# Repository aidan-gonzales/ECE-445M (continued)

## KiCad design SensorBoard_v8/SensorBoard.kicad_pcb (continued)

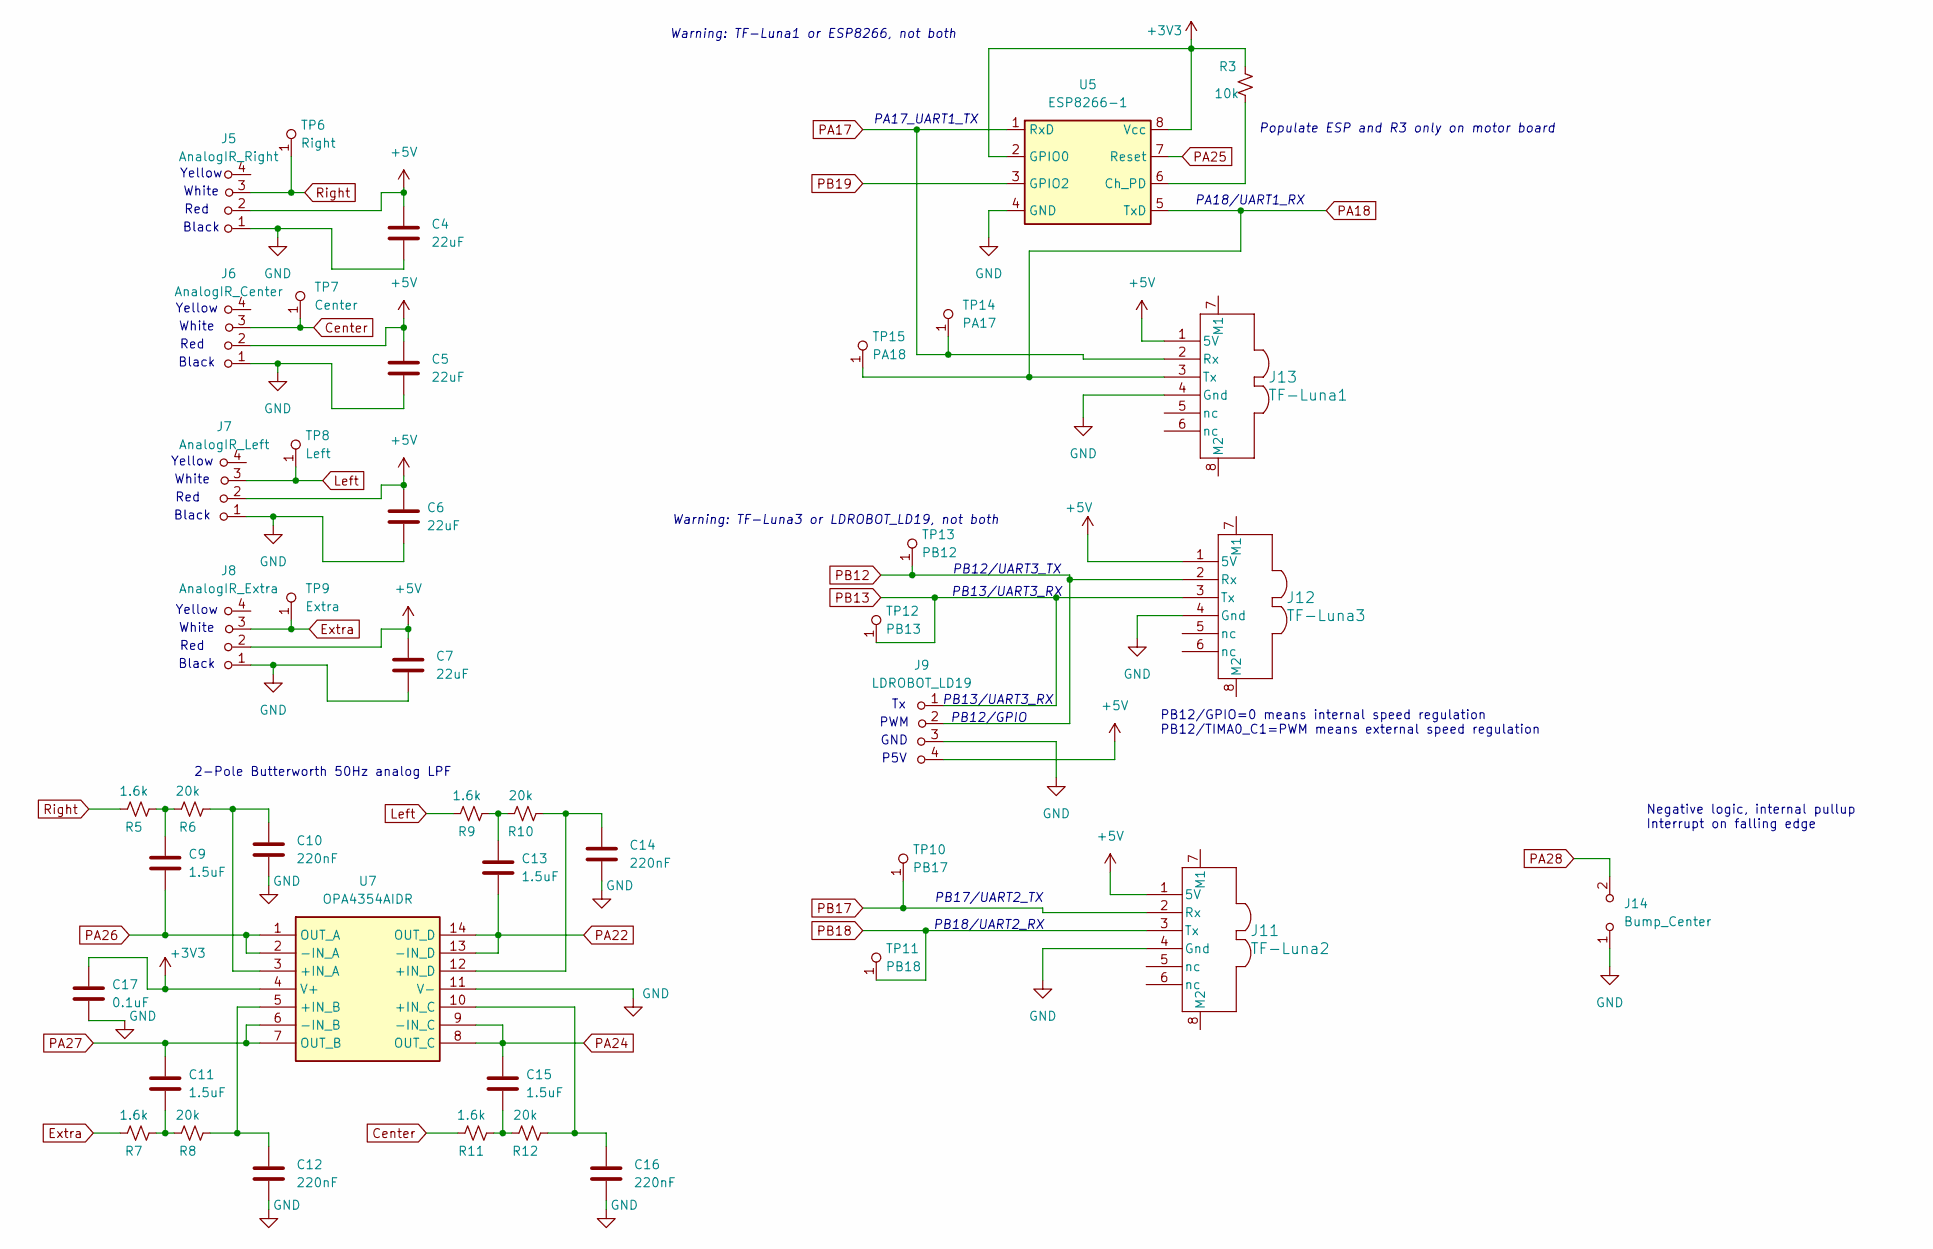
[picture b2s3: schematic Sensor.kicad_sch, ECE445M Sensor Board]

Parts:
C4, C5, C6, C7: 22uF; C_0805_2012Metric; LCSC C5186689
C9, C11, C13, C15: 1.5uF; C_0603_1608Metric; LCSC C5186689
C10, C12, C14, C16: 220nF; C_0603_1608Metric; LCSC C5186689
C17: 0.1uF; C_0603_1608Metric; LCSC C5186689
J5: AnalogIR_Right; PinHeader_1x04_P2.00mm_Horizontal; Mouser 713-110990037
J6: AnalogIR_Center; PinHeader_1x04_P2.00mm_Horizontal; Mouser 713-110990037
J7: AnalogIR_Left; PinHeader_1x04_P2.00mm_Horizontal; Mouser 713-110990037
J8: AnalogIR_Extra; PinHeader_1x04_P2.00mm_Horizontal; Mouser 713-110990037
J9: LDROBOT_LD19; PinHeader_1x04_P2.00mm_Horizontal_JST; Mouser 306-S04BPASK2LFSN
J11: TF-Luna2; CONN_SM06B-GHS-TB_JST; Digikey WM7624CT-ND
J12: TF-Luna3; CONN_SM06B-GHS-TB_JST; Digikey WM7624CT-ND
J13: TF-Luna1; CONN_SM06B-GHS-TB_JST; Digikey WM7624CT-ND
J14: Bump_Center; PinHeader_1x02_P2.54mm_Vertical
R3: 10k; R_Axial_DIN0204_L3.6mm_D1.6mm_P7.62mm_Horizontal
R5, R7, R9, R11: 1.6k; R_0603_1608Metric; LCSC C340542
R6, R8, R10, R12: 20k; R_0603_1608Metric; LCSC C340542
TP6: Right; Testpoint_1x1; Digikey 36-5000-ND, 36-5001-ND, 36-5002-ND , 36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
TP7: Center; Testpoint_1x1; Digikey 36-5000-ND, 36-5001-ND, 36-5002-ND , 36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
TP8: Left; Testpoint_1x1; Digikey 36-5000-ND, 36-5001-ND, 36-5002-ND , 36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
TP9: Extra; Testpoint_1x1; Digikey 36-5000-ND, 36-5001-ND, 36-5002-ND , 36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
TP10: PB17; Testpoint_1x1; Digikey 36-5000-ND, 36-5001-ND, 36-5002-ND , 36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
TP11: PB18; Testpoint_1x1; Digikey 36-5000-ND, 36-5001-ND, 36-5002-ND , 36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
TP12: PB13; Testpoint_1x1; Digikey 36-5000-ND, 36-5001-ND, 36-5002-ND , 36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
TP13: PB12; Testpoint_1x1; Digikey 36-5000-ND, 36-5001-ND, 36-5002-ND , 36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
TP14: PA17; Testpoint_1x1; Digikey 36-5000-ND, 36-5001-ND, 36-5002-ND , 36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
TP15: PA18; Testpoint_1x1; Digikey 36-5000-ND, 36-5001-ND, 36-5002-ND , 36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
U5: ESP8266-1; PinHeader_2x04_P2.54mm_Vertical
U7: OPA4354AIDR; SOIC127P600X175-14N; Mouser Part Number 595-OPA4354AIDR

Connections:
+3V3: C17.1, R3.1, U5.2 (GPIO0), U5.8 (Vcc), U7.4 (V+); also elsewhere on the board
+5V: C4.1, C5.1, C6.1, C7.1, J5.2 (5V), J6.2 (5V), J7.2 (5V), J8.2 (5V), J9.4 (5V), J11.1 (5V), J12.1 (5V), J13.1 (5V); also elsewhere on the board
Center: J6.3 (Vin), R11.1, TP7.1 (A)
Extra: J8.3 (Vin), R7.1, TP9.1 (A)
GND: C4.2, C5.2, C6.2, C7.2, C10.2, C12.2, C14.2, C16.2, C17.2, J5.1 (Gnd), J6.1 (Gnd), J7.1 (Gnd), J8.1 (Gnd), J9.3 (GND), J11.4 (Gnd), J12.4 (Gnd), J13.4 (Gnd), J14.1 (A), U5.4 (GND), U7.11 (V-); also elsewhere on the board
Left: J7.3 (Vin), R9.1, TP8.1 (A)
unnamed: C9.1, R5.2, R6.1
unnamed: C11.2, R7.2, R8.1
unnamed: C13.1, R9.2, R10.1
unnamed: C15.2, R11.2, R12.1
unnamed: R3.2, U5.6 (Ch_PD)
unnamed: C10.1, R6.2, U7.3 (+IN_A)
unnamed: C12.1, R8.2, U7.5 (+IN_B)
unnamed: C16.1, R12.2, U7.10 (+IN_C)
unnamed: C14.1, R10.2, U7.12 (+IN_D)
PA17: J13.2 (Rx), TP14.1 (A), U5.1 (RxD); also elsewhere on the board
PA18: J13.3 (Tx), TP15.1 (A), U5.5 (TxD); also elsewhere on the board
PA22: C13.2, U7.13 (-IN_D), U7.14 (OUT_D); also elsewhere on the board
PA24: C15.1, U7.8 (OUT_C), U7.9 (-IN_C); also elsewhere on the board
PA25: U5.7 (Reset); also elsewhere on the board
PA26: C9.2, U7.1 (OUT_A), U7.2 (-IN_A); also elsewhere on the board
PA27: C11.1, U7.6 (-IN_B), U7.7 (OUT_B); also elsewhere on the board
PA28: J14.2 (B); also elsewhere on the board
PB12: J9.2 (PWM), J12.2 (Rx), TP13.1 (A); also elsewhere on the board
PB13: J9.1 (Tx), J12.3 (Tx), TP12.1 (A); also elsewhere on the board
PB17: J11.2 (Rx), TP10.1 (A); also elsewhere on the board
PB18: J11.3 (Tx), TP11.1 (A); also elsewhere on the board
PB19: U5.3 (GPIO2); also elsewhere on the board
Right: J5.3 (Vin), R5.1, TP6.1 (A)

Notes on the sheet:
Black
Red
White
Yellow
PB12/UART3_TX
Warning: TF-Luna3 or LDROBOT_LD19, not both
Warning: TF-Luna1 or ESP8266, not both
PB12/GPIO
PB13/UART3_RX
Populate ESP and R3 only on motor board
PA17_UART1_TX
PB12/GPIO=0 means internal speed regulation PB12/TIMA0_C1=PWM means external speed regulation
PA18/UART1_RX
GND
P5V
PWM
Negative logic, internal pullup Interrupt on falling edge
2-Pole Butterworth 50Hz analog LPF
PB18/UART2_RX
PB17/UART2_TX

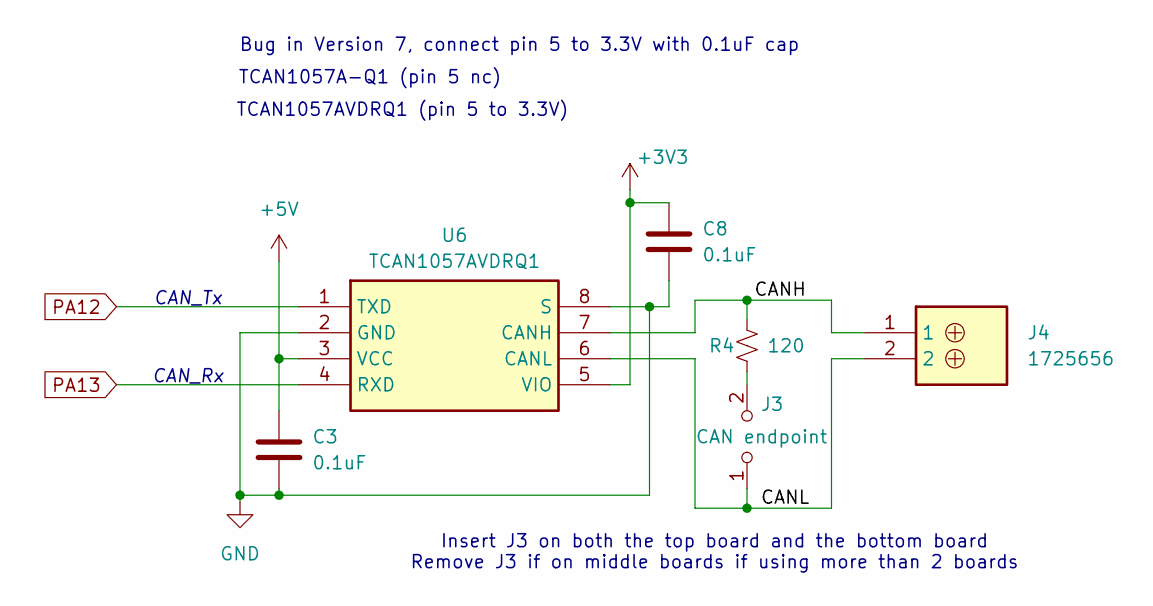
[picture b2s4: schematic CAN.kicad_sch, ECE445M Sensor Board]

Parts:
C3, C8: 0.1uF; C_0603_1608Metric; LCSC C5186689
J3: CAN endpoint; PinHeader_1x02_P2.54mm_Vertical
J4: 1725656; Mouser Part Number 651-1725656
R4: 120; R_0603_1608Metric; LCSC C340542
U6: TCAN1057AVDRQ1; SOIC127P600X175-8N; Mouser Part Number 595-TCAN1057AVDRQ1

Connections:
+3V3: C8.1, U6.5 (VIO); also elsewhere on the board
+5V: C3.1, U6.3 (VCC); also elsewhere on the board
/CAN Interface/CANH: J4.1, R4.1, U6.7 (CANH)
/CAN Interface/CANL: J3.1 (A), J4.2, U6.6 (CANL)
GND: C3.2, C8.2, U6.2 (GND), U6.8 (S); also elsewhere on the board
unnamed: J3.2 (B), R4.2
PA12: U6.1 (TXD); also elsewhere on the board
PA13: U6.4 (RXD); also elsewhere on the board

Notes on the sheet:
Insert J3 on both the top board and the bottom board Remove J3 if on middle boards if using more than 2 boards
CAN_Tx
Bug in Version 7, connect pin 5 to 3.3V with 0.1uF cap
TCAN1057AVDRQ1 (pin 5 to 3.3V)
TCAN1057A-Q1 (pin 5 nc)
CAN_Rx

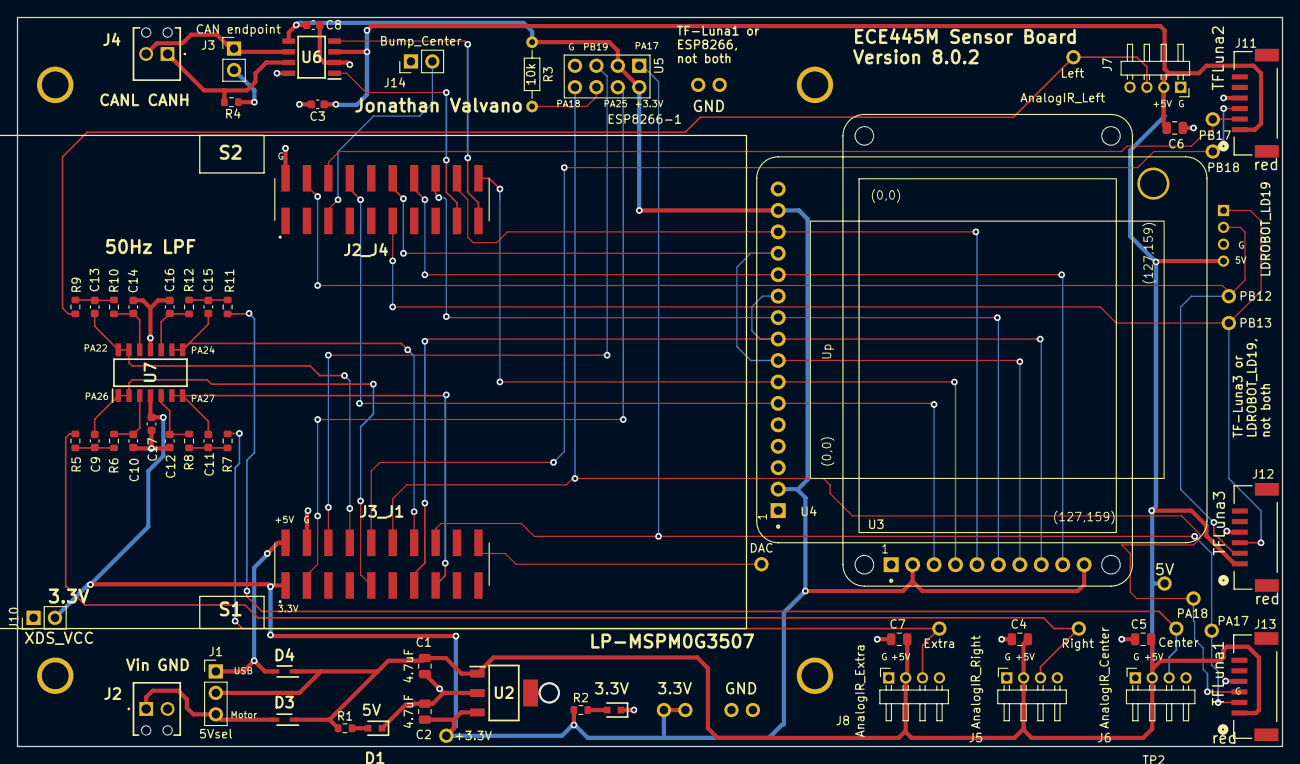
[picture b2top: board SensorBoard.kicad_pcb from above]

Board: 2 copper layers, 149.9 x 86.4 mm, 75 parts (1 on the bottom side), 46 nets.

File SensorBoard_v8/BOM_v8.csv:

Comment,Designator,Footprint,LCSC
4.7uF,"C1,C2",0805,C1779
0.1uF,"C3,C8,C17",0603,C1590
22uF,"C4,C5,C6,C7",0805,C45783
1.5uF,"C9,C11,C13,C15",0603,C361193
220nF,"C10,C12,C14,C16",0603,C519575
LED,"D1,D2","SMD,1.6x0.8mm",C5879214
BAT60AE6327,"D3,D4",SOD-323,C513277
LaunchPad,"J2_J4,J3_J1","SMD,P=2.54mm",C3294468
TF-Luna,"J11,J12,J13","SMD,P=1.25mm,Surface Mount，Right Angle",C17393620
1k,R1,0603,C21190
470,R2,0603,C23179
120,R4,0603,C22787
1.6k,"R5,R7,R9,R11",0603,C22847
20k,"R6,R8,R10,R12",0603,C4184
LM2937IMP-3.3/NOPB,U2,SOT-223,C140265
TCAN1057AVDRQ1,U6,SOIC-8,C3235000
OPA4354AIDR,U7,SOIC-14,C440031

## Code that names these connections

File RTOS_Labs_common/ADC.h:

/*!
 * @defgroup ADC
 * @brief Analog to digital conversion
  <table>
<caption id="ADCpins">ADC pins on the MSPM0G3507</caption>
<tr><th>Pin  <th>ADC channel<th>Sensor
<tr><td>PA27 <td>ADC0 channel 0 <td>J1.8 also MKII light interrupt
<tr><td>PA26 <td>ADC0 channel 1 <td>J1.6 MKII microphone in
<tr><td>PA25 <td>ADC0 channel 2 <td>J1.2 MKII Joystick X
<tr><td>PA24 <td>ADC0 channel 3 <td>J3.27 ***free***
<tr><td>PB25 <td>ADC0 channel 4 <td>J19.7 (insert 0ohm R74, no U3 OPA2365)
<tr><td>PB24 <td>ADC0 channel 5 <td>J1.5 also MKII joystick select button
<tr><td>PB20 <td>ADC0 channel 6 <td>J4.36 ***free***
<tr><td>PA22 <td>ADC0 channel 7 <td>J24 MKII Accelerometer Y

<tr><td>PA15 <td>ADC1 channel 0 <td>J3.30 (also DACout)
<tr><td>PA16 <td>ADC1 channel 1 <td>J3.29 ***free***
<tr><td>PA17 <td>ADC1 channel 2 <td>J3.28 ***free***
<tr><td>PA18 <td>ADC1 channel 3 <td>J3.26 MKII Joystick Y
<tr><td>PB17 <td>ADC1 channel 4 <td>J2.18 ***free***
<tr><td>PB18 <td>ADC1 channel 5 <td>J3.25 MKII Accelerometer Z
<tr><td>PB19 <td>ADC1 channel 6 <td>J3.23 MKII Accelerometer X
<tr><td>PA21 <td>ADC1 channel 7 <td>J17.8 (insert R20, remove R3)

</table>
 * @{*/
/**
 * @file      ADC.h
 * @brief     Initialize 12-bit ADC0 and/or ADC1
 * @details   ADC input, software trigger, 12-bit conversion<br>
 * The ADC allows two possible references: 2.5V or 3.3V.<br>
 * The internal 2.5V reference is lower noise, but limits the range to 0 to 2.5V.<br>
 * The other possibility is to use the analog voltage supply at 3.3V,
 * making the ADC range 0 to 3.3V. In this driver, the 3.3V range is selected.
 * There are several configurations (each with initialization and a
 * read ADC with software trigger, busy-wait function)<br>

 * @version   ECE319K v1.0
 * @author    Daniel Valvano and Jonathan Valvano
 * @copyright Copyright 2023 by Jonathan W. Valvano, valvano@mail.utexas.edu,
 * @warning   AS-IS
 * @note      For more information see  http://users.ece.utexas.edu/~valvano/
 * @date      August 13, 2023
 <table>
<caption id="ADCpins2">ADC pins on the MSPM0G3507</caption>
<tr><th>Pin  <th>ADC channel<th>Sensor
<tr><td>PA27 <td>ADC0 channel 0 <td>J1.8 also MKII light interrupt
<tr><td>PA26 <td>ADC0 channel 1 <td>J1.6 MKII microphone in
<tr><td>PA25 <td>ADC0 channel 2 <td>J1.2 MKII Joystick X
<tr><td>PA24 <td>ADC0 channel 3 <td>J3.27 ***free***
<tr><td>PB25 <td>ADC0 channel 4 <td>J19.7 (insert 0ohm R74, no U3 OPA2365)
<tr><td>PB24 <td>ADC0 channel 5 <td>J1.5 also MKII joystick select button
<tr><td>PB20 <td>ADC0 channel 6 <td>J4.36 ***free***
<tr><td>PA22 <td>ADC0 channel 7 <td>J24 MKII Accelerometer Y

<tr><td>PA15 <td>ADC1 channel 0 <td>J3.30 (also DACout)
<tr><td>PA16 <td>ADC1 channel 1 <td>J3.29 ***free***
<tr><td>PA17 <td>ADC1 channel 2 <td>J3.28 ***free***
<tr><td>PA18 <td>ADC1 channel 3 <td>J3.26 MKII Joystick Y
<tr><td>PB17 <td>ADC1 channel 4 <td>J2.18 ***free***
<tr><td>PB18 <td>ADC1 channel 5 <td>J3.25 MKII Accelerometer Z
<tr><td>PB19 <td>ADC1 channel 6 <td>J3.23 MKII Accelerometer X
<tr><td>PA21 <td>ADC1 channel 7 <td>J17.8 (insert R20, remove R3)

</table>
  ****note to students****<br>
  the data sheet says the ADC does not work when clock is 80 MHz
  however, the ADC seems to work on my boards at 80 MHz
  I suggest you try 80MHz, but if it doesn't work, switch to 40MHz
  ******************************************************************************/



//#ifndef __ADC_H__
//#define __ADC_H__
#include <ti/devices/msp/msp.h>
#include <stdint.h>
/**
 * \brief using ADCVREF_INT means choose internal 2.5V reference for accuracy
 */
#define ADCVREF_INT  0x200
/**
 * \brief using ADCVREF_EXT means choose external reference not tested
 */ 
#define ADCVREF_EXT  0x100
/**
 * \brief using ADCVREF_VDDA means choose power line 3.3V reference for 0 to 3.3V range
 */
#define ADCVREF_VDDA 0x000

/**
 * Initialize 12-bit ADC0 in software-triggered mode to take
 * measurements when the associated function is called.
 * One channel is to be measured
 * @param channel is the 0 to 7
 * @param reference is ADCVREF_INT, ADCVREF_EXT, ADCVREF_VDDA
 * @return none 
 * @brief  Initialize 12-bit ADC0
 */
void ADC0_Init(uint32_t channel, uint32_t reference);

/**
 * Trigger a single ADC0 measurement,
 * wait for it to complete, and return the 12-bit result
 * as 0 to 4095.
 * The ADC input voltage range is 0 to 3.3V.
 * Busy-wait synchronization used.
 * @param none
 * @return 12-bit result
 * @note  Assumes ADC0_Init has been called.
 * @brief  Trigger ADC measurement and wait for result.
 */
uint32_t ADC0_In(void);

/**
 * Initialize 12-bit ADC1 in software-triggered mode to take
 * measurements when the associated function is called.
 * One channel is to be measured
 * @param channel is the 0 to 7
 * @param reference is ADCVREF_INT, ADCVREF_EXT, ADCVREF_VDDA
 * @return none 
 * @brief  Initialize 12-bit ADC0
 */
void ADC1_Init(uint32_t channel, uint32_t reference);

/**
 * Trigger a single ADC1 measurement,
 * wait for it to complete, and return the 12-bit result
 * as 0 to 4095.
 * The ADC input voltage range is 0 to 3.3V.
 * Busy-wait synchronization used.
 * @param none
 * @return 12-bit result
 * @note  Assumes ADC1_Init has been called.
 * @brief  Trigger ADC measurement and wait for result.
 */
uint32_t ADC1_In(void);

/**
 * Initialize 12-bit ADC0 or ADC1 in software-triggered mode to take
 * measurements when the associated function is called.
 * One channel is to be measured
 * @param adc12 is ADC0 or ADC1
 * @param channel is the 0 to 7
 * @param reference is ADCVREF_INT, ADCVREF_EXT, ADCVREF_VDDA
 * @return none
 * @brief  Initialize 12-bit ADC0
 */
void ADC_Init(ADC12_Regs *adc12, uint32_t channel, uint32_t reference);

/**
 * Trigger a single ADC0 or ADC1 measurement,
 * wait for it to complete, and return the 12-bit result
 * as 0 to 4095.
 * The ADC input voltage range is 0 to 3.3V.
 * Busy-wait synchronization used.
 * @param adc12 is ADC0 or ADC1
 * @return 12-bit result
 * @note  Assumes ADC_Init has been called.
 * @brief  Trigger ADC measurement and wait for result.
 */
uint32_t ADC_In(ADC12_Regs *adc12);

/**
 * Initialize 12-bit ADC0 or ADC1 in software-triggered mode to take
 * measurements when the associated function is called.
 * Two channels are to be measured
 * @param adc12 is ADC0 or ADC1
 * @param channel1 is the 0 to 7
 * @param channel2 is the 0 to 7
 * @param reference is ADCVREF_INT, ADCVREF_EXT, ADCVREF_VDDA
 * @return none 
 * @brief  Initialize 12-bit ADC for two channels
 */
void ADC_InitDual(ADC12_Regs *adc12, uint32_t channel1, uint32_t channel2, uint32_t reference);

/**
 * Trigger a dual ADC0 or ADC1 measurement,
 * wait for it to complete, and return the two 12-bit results
 * as 0 to 4095.
 * The ADC input voltage range is 0 to 3.3V.
 * Busy-wait synchronization used.
 * @param adc12 is ADC0 or ADC1
 * @param *d1 address into which the first ADC sample will be stored
 * @param *d2 address into which the second ADC sample will be stored
 * @return none 
 * @note  Assumes ADC_InitDual has been called.
 * @brief  Trigger two ADC measurements and wait for results.
 */
void ADC_InDual(ADC12_Regs *adc12, uint32_t *d1, uint32_t *d2);

/**
 * Initialize 12-bit ADC0 or ADC1 in software-triggered mode to take
 * measurements when the associated function is called.
 * three channels are to be measured
 * @param adc12 is ADC0 or ADC1
 * @param channel1 is the 0 to 7
 * @param channel2 is the 0 to 7
 * @param channel3 is the 0 to 7
 * @param reference is ADCVREF_INT, ADCVREF_EXT, ADCVREF_VDDA
 * @return none
 * @brief  Initialize 12-bit ADC for three channels
 */
void ADC_InitTriple(ADC12_Regs *adc12,uint32_t channel1,uint32_t channel2,uint32_t channel3,uint32_t reference);

/**
 * Trigger a triple ADC0 or ADC1 measurement,
 * wait for it to complete, and return the three 12-bit results
 * as 0 to 4095.
 * The ADC input voltage range is 0 to 3.3V.
 * Busy-wait synchronization used.
 * @param adc12 is ADC0 or ADC1
 * @param *d1 address into which the first ADC sample will be stored
 * @param *d2 address into which the second ADC sample will be stored
 * @param *d3 address into which the third ADC sample will be stored
 * @return none
 * @note  Assumes ADC_InitTriple has been called.
 * @brief  Trigger three ADC measurements and wait for results.
 */
void ADC_InTriple(ADC12_Regs *adc12,uint32_t *d1, uint32_t *d2, uint32_t *d3);

/**
 * Initialize 12-bit ADC0 in software-triggered mode to take
 * measurements when the associated function is called.
 * One channel is to be measured 2^n times in average.
 * @param channel is the 0 to 7
 * @param n 0 to 7
 * @return none 
 * @brief  Initialize 12-bit ADC0 for hardware averaging
 * @note uses ADCVREF_VDDA, so range is 0 to 3.3V
 */
void ADC0_InitAve(uint32_t channel, uint32_t n);

//#endif //  __ADC_H__
/** @}*/

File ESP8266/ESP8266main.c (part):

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 |                        4   5 |
 \------------------------------/ 
 Connects MSPM0 
    UART1 on (PA17/PA18) or UART2 on (PB17/PB18)
    Reset on PA25
    Ok to not access PB19 because of the internal pullup in ESP8266
 ESP8266    MSPM0     Motor board version 7
  1 URxD    PA17      UART1 out of MSPM0, into ESP8266 115200 baud
  2 GPIO0             +3.3V for normal operation (ground to flash)
  3 GPIO2   PB19      GPIO, high/float on startup, has internal pullup, can be used for I/O
  4 GND     Gnd       GND (70mA)
  5 UTxD    PA18      UART out of ESP8266, UART1 into MSPM0 115200 baud
  6 Ch_PD             chip select, 10k resistor to 3.3V
  7 Reset   PA25      MSPM0 GPIO output, can issue output low to cause hardware reset
  8 Vcc               regulated 3.3V supply with at least 70mA

 ESP8266    MSPM0     Motor board version 7.1
  1 URxD    PB17      UART2 out of MSPM0, into ESP8266 115200 baud
  2 GPIO0             +3.3V for normal operation (ground to flash)
  3 GPIO2   PB19      GPIO, high/float on startup, has internal pullup, can be used for I/O
  4 GND     Gnd       GND (70mA)
  5 UTxD    PB18      UART out of ESP8266, UART2 into MSPM0 115200 baud
  6 Ch_PD             chip select, 10k resistor to 3.3V
  7 Reset   PA25      MSPM0 GPIO output, can issue output low to cause hardware reset
  8 Vcc               regulated 3.3V supply with at least 70mA
 */
 /* Derived from i2c_controller_rw_multibyte_fifo_poll_LP_MSPM0G3507_nortos_ticlang
  VCC to +3.3V
  I2C SCL: PB2 is the SSD1306 SCL, with 1.5k pullup to 3.3V
  I2C SDA: PB3 is the SSD1306 SDA
  GND to GND
*/

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
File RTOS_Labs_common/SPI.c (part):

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// **********ST7735 TFT and SDC*******************
// ST7735
// Backlight (pin 10)     to +3.3 V
// MISO (pin 9)           from SPI1 POCI PB7
// SCK (pin 8)            to SPI1 SCLK: PB9
// MOSI (pin 7)           to SPI1 PICO: PB8
// TFT_CS (pin 6)         to LCD, GPIO:  PB6
// CARD_CS (pin 5)        to SDC, GPIO PB0
// Data/Command (pin 4)   to PB16 (GPIO), high for data, low for command
// RESET (pin 3)          to PB15 (GPIO)
// VCC (pin 2)            to +3.3 V
// Gnd (pin 1)            to ground

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// ST7735
// LED-   (pin 16) TFT, to ground
// LED+   (pin 15) TFT, to +3.3 V
// SD_CS  (pin 14) SDC, to chip select, GPIO PB0
// MOSI   (pin 13) SDC, to MOSI PB8  MOSI SPI1 PICO
// MISO   (pin 12) SDC, to MISO from SPI1 POCI PB7
// SCK    (pin 11) SDC, to serial clock
// CS     (pin 10) TFT, // TFT_CS to LCD, GPIO:  PB6
// SCL    (pin 9)  TFT, to PB9  SPI1 SCLK
// SDA    (pin 8)  TFT, to PB8  MOSI SPI1 PICO
// A0     (pin 7)  TFT, to PB16 Data/Command, high for data, low for command
// RESET  (pin 6)  TFT, to PB15 reset (GPIO), low to reset
// NC     (pins 3,4,5)
// VCC    (pin 2)       to +3.3 V
// GND    (pin 1)       to ground
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    //   bits 31-24 unlock key 0x26
    //   bit 0 is Enable Power
  SPI1->GPRCM.PWREN = 0x26000001;
  // configure PB9 PB6 PB8 as alternate SPI1 function
  IOMUX->SECCFG.PINCM[PB9INDEX]  = 0x00000083;  // SPI1 SCLK
  IOMUX->SECCFG.PINCM[PB6INDEX]  = 0x00000083;  // SPI1 CS0
  IOMUX->SECCFG.PINCM[PB8INDEX]  = 0x00000083;  // SPI1 PICO
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  IOMUX->SECCFG.PINCM[PB16INDEX] = 0x00000081;  // GPIO output, LCD RS
// **  IOMUX->SECCFG.PINCM[PA13INDEX] = 0x00000081;  // GPIO output, LCD RS
  Clock_Delay(24); // time for gpio to power up
// **  GPIOA->DOE31_0 |= 1<<13;    // PA13 is LCD RS
  GPIOB->DOE31_0 |= 1<<16;    // PA13 is LCD RS
  GPIOB->DOE31_0 |= 1<<15;    // PB15 is LCD !RST
  GPIOB->DOUTSET31_0 = 1<<16; // RS=1
// **  GPIOA->DOUTSET31_0 = 1<<13; // RS=1
  GPIOB->DOUTSET31_0 = 1<<15; // !RST = 1
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// Output: none
void SPI_OutData(char data){
  while((SPI1->STAT&0x02) == 0x00){}; // spin if TxFifo full
  GPIOA->DOUTSET31_0 = 1<<13;         // RS=PA13=1 for data
  SPI1->TXDATA = data;
}
 //---------SPI_OutCommand------------
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 // Output: none
 void SPI_OutCommand(char command){
   while((SPI1->STAT&0x10) == 0x10){}; // spin if SPI busy
   GPIOA->DOUTCLR31_0 = 1<<13;         // RS=PA13=0 for command
   SPI1->TXDATA = command;
   while((SPI1->STAT&0x10) == 0x10){}; // spin if SPI busy
 }
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void CS_Init(void){
  IOMUX->SECCFG.PINCM[SDC_CS_INDEX]  = (uint32_t) 0x00000081;
  SDC_CS->DOE31_0 |= SDC_CS_PIN;
  SDC_CS_HIGH(); // PB0=1
}

 //---------SPI1_Reset------------
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 // Input: none
 // Output: none
 void SPI1_Reset(void){
   TFT_RST_HIGH();        // PB15=!RST=1
   Clock_Delay1ms(500);   // 500ms (calibrated with logic analyzer)
   TFT_RST_LOW();         // PB15=!RST=0
   Clock_Delay1ms(500);   // 500ms
   TFT_RST_HIGH();        // PB15=!RST=1
   Clock_Delay1ms(500);   // 500ms
 }

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      //   bits 31-24 unlock key 0x26
      //   bit 0 is Enable Power
  SPI1->GPRCM.PWREN = 0x26000001;
    // configure PB9 PB6 PB8 as alternate SPI1 function
  IOMUX->SECCFG.PINCM[PB9INDEX]  = 0x00000083;  // SPI1 SCLK
  IOMUX->SECCFG.PINCM[PB8INDEX]  = 0x00000083;  // SPI1 PICO
  IOMUX->SECCFG.PINCM[TFT_RST_INDEX] = 0x00000081;  // GPIO output, LCD !RST
  IOMUX->SECCFG.PINCM[TFT_DC_INDEX] = 0x00000081;  // GPIO output, LCD D/C RS
  IOMUX->SECCFG.PINCM[PB7INDEX]  = 0x00040083;  // SPI1 POCI
  IOMUX->SECCFG.PINCM[TFT_CS_INDEX]  = 0x00000081;  // PB6 is regular GPIO
  Clock_Delay(24); // time for gpio to power up
  TFT_DC->DOE31_0 |= TFT_DC_PIN;    // PB16 is LCD RS
  TFT_DC_HIGH();
  TFT_RST->DOE31_0 |= TFT_RST_PIN; 
  TFT_RST_HIGH();
  TFT_CS->DOE31_0 |= TFT_CS_PIN;   // PB6 is regular GPIO
  TFT_CS_HIGH();                   // disable LCD

  SPI1->CLKSEL = 8; // SYSCLK
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// Output: none
void TFT_OutData(char data){char response;
  while((SPI1->STAT&0x10) == 0x10){}; // spin if SPI busy
  SDC_CS_HIGH();  // PB0 high, disable SDC
  TFT_CS_LOW();   // PB6 low, enable TFT
  TFT_DC_HIGH();  // RS=PB16=1 for data
  SPI1->TXDATA = data;
  while((SPI1->STAT&0x04) == 0x04){}; // spin SPI RxFifo empty
  response = SPI1->RXDATA; // has no meaning, flush
  TFT_CS_HIGH();  // PB6 high
}
 //---------TFT_OutCommand------------
 // Output 8-bit command to SPI port
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 // Output: none
 void TFT_OutCommand(char command){char response;
   while((SPI1->STAT&0x10) == 0x10){}; // spin if SPI busy
   SDC_CS_HIGH(); // PB0 high, disable SDC
   TFT_CS_LOW();  // PB6 low, enable TFT
   TFT_DC_LOW();  // RS=PB16=0 for command
   SPI1->TXDATA = command;
   while((SPI1->STAT&0x10) == 0x10){}; // spin if SPI busy
   response = SPI1->RXDATA; // has no meaning, flush
   TFT_CS_HIGH();  // PB6 high
 }
 
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
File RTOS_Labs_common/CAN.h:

// CAN.h
// Runs on MSPM0G3507
// Use FDCAN0 to communicate on CAN bus PA12 and PA13
// 

// Jonathan Valvano
// December 11, 2025
// derived from can_to_uart_bridge_LP_MSPM0G3507_nortos_ticlang
/* 
 Copyright 2025 by Jonathan W. Valvano, valvano@mail.utexas.edu
    You may use, edit, run or distribute this file
    as long as the above copyright notice remains
 THIS SOFTWARE IS PROVIDED "AS IS".  NO WARRANTIES, WHETHER EXPRESS, IMPLIED
 OR STATUTORY, INCLUDING, BUT NOT LIMITED TO, IMPLIED WARRANTIES OF
 MERCHANTABILITY AND FITNESS FOR A PARTICULAR PURPOSE APPLY TO THIS SOFTWARE.
 VALVANO SHALL NOT, IN ANY CIRCUMSTANCES, BE LIABLE FOR SPECIAL, INCIDENTAL,
 OR CONSEQUENTIAL DAMAGES, FOR ANY REASON WHATSOEVER.
 For more information about my classes, my research, and my books, see
 http://users.ece.utexas.edu/~valvano/
 */
// Use TCAN1057AVDRQ1 (not TCAN1057A-Q1, the version with pin 5 nc)
//  Pin1 TXD  ---- CAN_Tx PA12 FD-CAN module 0 transmit
//  Pin2 Vss  ---- ground
//  Pin3 VCC  ---- +5V with 0.1uF cap to ground
//  Pin4 RXD  ---- CAN_Rx PA13 FD-CAN module 0 receive (0 to 3.3V)
//  Pin5 VIO  ---- +3.3V (digital interface supply)
//  Pin6 CANL ---- to other CANL on network 
//  Pin7 CANH ---- to other CANH on network 
//  Pin8 RS   ---- ground, Slope-Control Input (maximum slew rate)
// 120 ohm across CANH, CANL on both ends of network

#ifndef __CAN_H__
#define __CAN_H__
#include <stdint.h>

void CAN_Init(void);

void CAN_EnableInterrupts(uint32_t priority);

// 0 if failure
// 1 if ok
int CAN_Send(uint32_t id, uint32_t dlc, uint8_t *data);

// Returns 1 if receive data is available
//         0 if no receive data ready
int CAN_CheckMail(void);

// if receive data is ready, gets the data and returns true
// if no receive data is ready, returns false
int CAN_GetMailNonBlock(uint32_t *id, uint32_t *dlc, uint8_t *data);

// if receive data is ready, gets the data 
// if no receive data is ready, it waits until it is ready
void CAN_GetMail(uint32_t *id, uint32_t *dlc, uint8_t *data);

#endif //  __CAN_H__

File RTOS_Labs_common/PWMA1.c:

/* PWMA1.c
 * Jonathan Valvano
 * November 24, 2025
 * Derived from timx_timer_mode_pwm_edge_sleep_LP_MSPM0G3507_nortos_ticlang
 
 */

/*
 * Copyright (c) 2026, Texas Instruments Incorporated
 * All rights reserved.
 *
 * Redistribution and use in source and binary forms, with or without
 * modification, are permitted provided that the following conditions
 * are met:
 *
 * *  Redistributions of source code must retain the above copyright
 *    notice, this list of conditions and the following disclaimer.
 *
 * *  Redistributions in binary form must reproduce the above copyright
 *    notice, this list of conditions and the following disclaimer in the
 *    documentation and/or other materials provided with the distribution.
 *
 * *  Neither the name of Texas Instruments Incorporated nor the names of
 *    its contributors may be used to endorse or promote products derived
 *    from this software without specific prior written permission.
 *
 * THIS SOFTWARE IS PROVIDED BY THE COPYRIGHT HOLDERS AND CONTRIBUTORS "AS IS"
 * AND ANY EXPRESS OR IMPLIED WARRANTIES, INCLUDING, BUT NOT LIMITED TO,
 * THE IMPLIED WARRANTIES OF MERCHANTABILITY AND FITNESS FOR A PARTICULAR
 * PURPOSE ARE DISCLAIMED. IN NO EVENT SHALL THE COPYRIGHT OWNER OR
 * CONTRIBUTORS BE LIABLE FOR ANY DIRECT, INDIRECT, INCIDENTAL, SPECIAL,
 * EXEMPLARY, OR CONSEQUENTIAL DAMAGES (INCLUDING, BUT NOT LIMITED TO,
 * PROCUREMENT OF SUBSTITUTE GOODS OR SERVICES; LOSS OF USE, DATA, OR PROFITS;
 * OR BUSINESS INTERRUPTION) HOWEVER CAUSED AND ON ANY THEORY OF LIABILITY,
 * WHETHER IN CONTRACT, STRICT LIABILITY, OR TORT (INCLUDING NEGLIGENCE OR
 * OTHERWISE) ARISING IN ANY WAY OUT OF THE USE OF THIS SOFTWARE,
 * EVEN IF ADVISED OF THE POSSIBILITY OF SUCH DAMAGE.
 */
//#define CONFIG_MSPM0G350X
//#define SYSCONFIG_WEAK __attribute__((weak))
#include <ti/devices/msp/msp.h>
#include "../inc/LaunchPad.h"
#include "../RTOS_Labs_common/PWMA1.h"
#include "../inc/Clock.h"
//  Timer A1  is on Power domain PD1
// for 32MHz bus clock, Timer clock is 32MHz
// for 40MHz bus clock, Timer clock is MCLK 40MHz
// for 80MHz bus clock, Timer clock is MCLK 80MHz
// CCP0 PWM output on PB4
// CCP1 PWM output on PB1
// PB4/TIMA1_C0;
// PB1/TIMA1_C1;

uint32_t PWMA1_Period;
// Initialize PWM outputs on PA12 PA13
// Rising edge synchronized
// timerClkSrc = 2 for 32768 Hz LFCLK
//             = 4 for 4MHz MFCLK
//             = 8 for 80/40/32/4 BUSCLK
// divide clock by timerClkPrescale+1, 0 to 255
// period sets the PWM period
// timerClkSrc could be 40MHz, 32MHz, 4MHz, or 32767Hz
// timerClkDivRatio = 1
// PWMFreq = (timerClkSrc / (timerClkDivRatio * (timerClkPrescale + 1) * period))
// For example, source=LFCLK, prescale=0, period = 1000, PWM frequency = 32.768 Hz
// For example, source=BUSCLK, 80MHz bus, prescale=39, period = 10000, PWM frequency = 200Hz
void PWMA1_Init(uint32_t timerClkSrc, uint32_t timerClkPrescale, uint32_t period, uint32_t duty0, uint32_t duty1){
  TIMA1->GPRCM.RSTCTL = (uint32_t)0xB1000003;
  TIMA1->GPRCM.PWREN = (uint32_t)0x26000001;
  Clock_Delay(2); // time for TimerA1 to power up
  IOMUX->SECCFG.PINCM[PB4INDEX]  = 0x00000084; // TIMA1 output CCP0
  IOMUX->SECCFG.PINCM[PB1INDEX]  = 0x00000084; // TIMA1 output CCP1
  GPIOB->DOE31_0 |= (1<<4)|(1<<1);
  TIMA1->CLKSEL = timerClkSrc; // 8=BUSCLK, 4= MFCLK, 2= LFCLK clock
  TIMA1->CLKDIV = 0x00; // divide by 1
  TIMA1->COMMONREGS.CPS = timerClkPrescale;     // divide by prescale+1,
  // 32768Hz/256 = 256Hz, 7.8125
  TIMA1->COUNTERREGS.LOAD  = period-1;  // reload register sets period
  PWMA1_Period = period;
  TIMA1->COUNTERREGS.CTRCTL = 0x02;
  // bits 5-4 CM =0, down
  // bits 3-1 REPEAT =001, continue
  // bit 0 EN enable (0 for disable, 1 for enable)
  TIMA1->COUNTERREGS.CCCTL_01[0] = 0; // no capture
  TIMA1->COUNTERREGS.CCCTL_01[1] = 0; // no capture
  // COC compare mode
  TIMA1->GEN_EVENT0.IMASK = 0x00; // no interrupts
  TIMA1->COMMONREGS.CCPD = 0x03;  // output CCP1 CCP0
  TIMA1->COMMONREGS.CCLKCTL = 1;
  TIMA1->COUNTERREGS.CC_01[0] = duty0;
  TIMA1->COUNTERREGS.CC_01[1] = duty1;
  TIMA1->COUNTERREGS.OCTL_01[0] = 0x0000; // connected to PWM
  TIMA1->COUNTERREGS.OCTL_01[1] = 0x0000; // connected to PWM
  TIMA1->COUNTERREGS.CCACT_01[0] = 0x0088;
  TIMA1->COUNTERREGS.CCACT_01[1] = 0x0088;
  // bits 10-9 CUACT 0 for no action on up compare
  // bits 7-6 CDACT 10 for make low on compare event down
  // bits 4-3 LACT 01 for make high on load event
  // bits 1-0 ZACT 00 for no action on zero event
  TIMA1->COUNTERREGS.CTRCTL |= 0x01;
}
void PWMA1_SetDuty(uint32_t duty0, uint32_t duty1){
  IOMUX->SECCFG.PINCM[PB4INDEX]  = 0x00000084; // PB4 TIMA1 output CCP0 PWM low
  IOMUX->SECCFG.PINCM[PB1INDEX]  = 0x00000084; // PB1 TIMA1 output CCP1 PWM low
  TIMA1->COUNTERREGS.CC_01[0] = duty0;
  TIMA1->COUNTERREGS.CC_01[1] = duty1;
}

void PWMA1_Forward(uint32_t duty0){
  IOMUX->SECCFG.PINCM[PB4INDEX]  = 0x00000084; // PB4 TIMA1 output CCP0 PWM low
  IOMUX->SECCFG.PINCM[PB1INDEX]  = 0x00000081; // PB1 GPIO=high
  GPIOB->DOUTSET31_0 = 1<<1;  // PB1=1
  TIMA1->COUNTERREGS.CC_01[0] = duty0;
}
void PWMA1_Backward(uint32_t duty1){
  IOMUX->SECCFG.PINCM[PB4INDEX]  = 0x00000081; // PB4 GPIO=high
  IOMUX->SECCFG.PINCM[PB1INDEX]  = 0x00000084; // PB1 TIMA1 output CCP1 PWM low
  GPIOB->DOUTSET31_0 = 1<<4;  // PB4=1
  TIMA1->COUNTERREGS.CC_01[1] = duty1;
}
void PWMA1_Break(void){
  IOMUX->SECCFG.PINCM[PB4INDEX]  = 0x00000081; // PB4 GPIO=high
  IOMUX->SECCFG.PINCM[PB1INDEX]  = 0x00000081; // PB1 GPIO=high
  GPIOB->DOUTSET31_0 = (1<<4)|(1<<1);  // PB4=1,PB1=1
}
void PWMA1_Coast(void){ // will sleep after 1ms
  IOMUX->SECCFG.PINCM[PB4INDEX]  = 0x00000081; // PB4 GPIO=high
  IOMUX->SECCFG.PINCM[PB1INDEX]  = 0x00000081; // PB1 GPIO=high
  GPIOB->DOUTCLR31_0 = (1<<4)|(1<<1);  // PB4=0,PB1=0
}

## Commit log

2026-02-13 lab2 working
2026-02-17 lab 2 complete
2026-02-17 Lab 3 Testmain1, 2, and 3 working
2026-02-23 lab 3 in progress before schedule finder changes
2026-02-26 lab 3 done
2026-03-10 lab 3 working version
2026-03-11 lab4 done
2026-03-30 lab5 done
